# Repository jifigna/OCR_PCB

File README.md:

En la carpeta OCR_AEREO_HELTEC_V1 se encuentra el proyecto KiCad con los esquemáticos y PCB del diseño de adaptación del OCR al HELTEC V4. 

El mismo se creó utilizando la versión KiCad 10.0

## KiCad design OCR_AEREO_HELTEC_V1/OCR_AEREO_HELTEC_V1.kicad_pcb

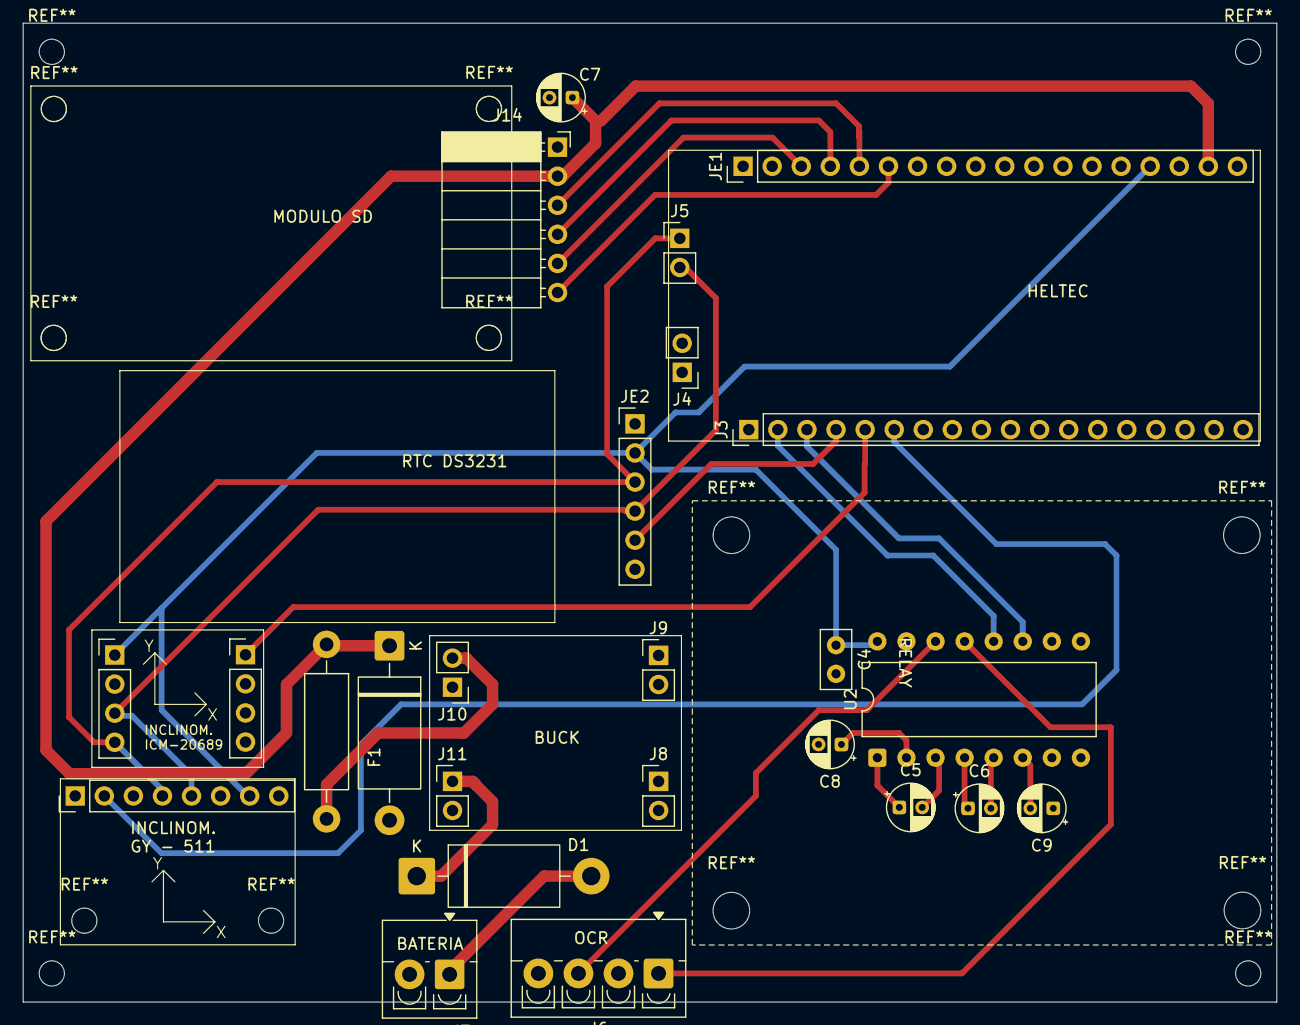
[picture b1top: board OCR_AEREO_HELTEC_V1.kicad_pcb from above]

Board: 2 copper layers, 109.5 x 85.5 mm, 25 parts (0 on the bottom side), 25 nets.

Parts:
C4: 0.1 uF; C_Disc_D5.0mm_W2.5mm_P2.50mm
C5, C6, C8, C9: 0.1uF; CP_Radial_D4.0mm_P2.00mm
C7: 470uF; CP_Radial_D4.0mm_P2.00mm
D1: 1N5402; D_DO-201AD_P15.24mm_Horizontal
D2: 1N53xxB; D_DO-201_P15.24mm_Horizontal
F1: Fuse; R_Axial_DIN0411_L9.9mm_D3.6mm_P15.24mm_Horizontal
J1, J2: Conn_01x04_Socket; PinHeader_1x04_P2.54mm_Vertical
J3: Conn_01x18_Pin; PinHeader_1x18_P2.54mm_Vertical
J4, J5, J8, J9, J10, J11: Conn_01x02_Pin; PinHeader_1x02_P2.54mm_Vertical
J6: OCR; TerminalBlock_4Ucon_1x04_P3.50mm_Vertical
J7: BATERÍA; TerminalBlock_4Ucon_1x02_P3.50mm_Vertical
J12: Conn_01x08_Socket; PinHeader_1x08_P2.54mm_Vertical
J14: MODULO SD; PinSocket_1x06_P2.54mm_Horizontal
JE1: Conn_01x18_Pin; PinHeader_1x18_P2.54mm_Vertical
JE2: RTC_DS3231; PinHeader_1x06_P2.54mm_Vertical
U2: MAX3232; DIP-16_W10.16mm

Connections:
5V: C7.1, D2.1 (K), F1.1, J14.2, JE1.17
BATERIA: D1.2 (A), J7.1
CLK_SPI: J14.5, JE1.3
CS_SD: J14.6, JE1.6
GND: C4.2, C7.2, C8.2, C9.1, D2.2 (A), J1.2, J2.4, J3.18, J6.2, J7.2, J8.1 (Pin_1_1), J9.2 (Pin_2_2), J12.6, J14.1, JE2.1, U2.15 (GND)
HELTEC_TO_OCR: J3.3, U2.11 (T1IN)
INT_INCL_1: J2.1, J3.5
INT_INCL_2: J3.6, J12.2
IN_BUCK: D1.1 (K), J11.1 (Pin_1_1)
MISO: J14.3, JE1.5
MOSI: J14.4, JE1.4
unnamed: C5.1, U2.1 (C1+)
unnamed: C5.2, U2.3 (C1-)
unnamed: C6.1, U2.4 (C2+)
unnamed: C6.2, U2.5 (C2-)
unnamed: C8.1, U2.2 (VS+)
unnamed: C9.2, U2.6 (VS-)
OCR_TO_HELTEC: J3.2, U2.12 (R1OUT)
OUT_BUCK: F1.2, J10.2 (Pin_2_2)
RX_OCR: J6.3, U2.14 (T1OUT)
SCL: J1.3, J5.2, J12.5, JE2.4
SDA: J1.4, J5.1, J12.4, JE2.3
SQW: J3.4, JE2.5
TX_OCR: J6.1, U2.13 (R1IN)
Vext: C4.1, J1.1, J12.7, JE1.15, JE2.2, U2.16 (VCC)

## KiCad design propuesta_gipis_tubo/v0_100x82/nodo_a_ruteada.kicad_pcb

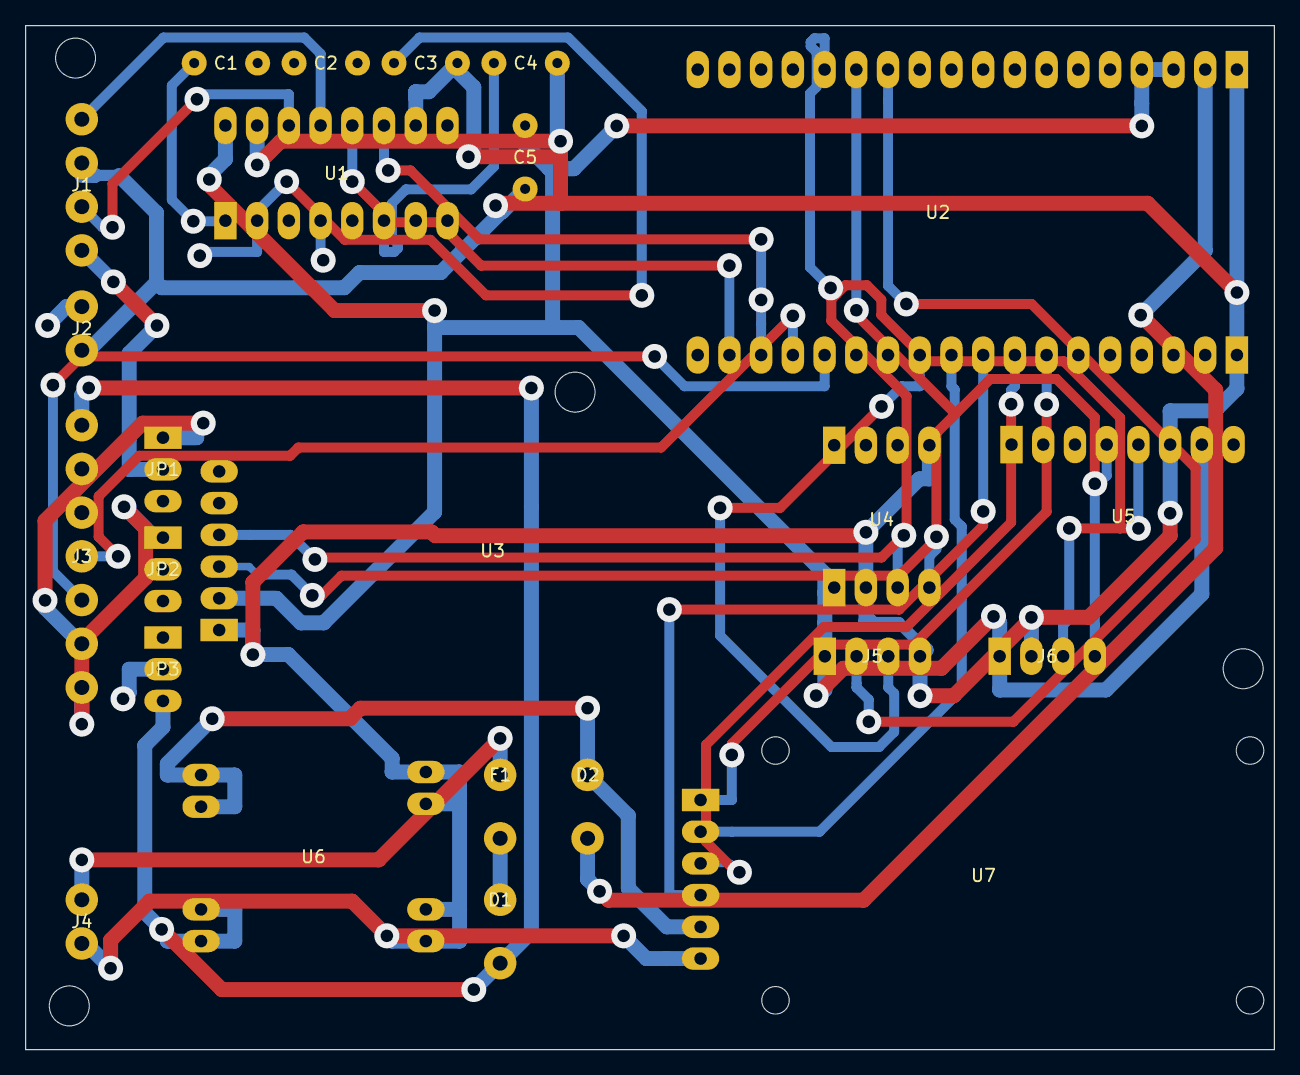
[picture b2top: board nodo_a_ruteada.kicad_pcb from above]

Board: 2 copper layers, 100.0 x 82.0 mm, 24 parts (0 on the bottom side), 32 nets.

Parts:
C1, C2, C3, C4, C5: 100n
D1, D2: 1N5819
F1: FUSE_1A
J1: OCR
J2: BIOSHUTTER
J3: RELE_EXT
J4: BAT_12V
J5: GPS
J6: I2C_AUX
JP1: OCR_PWR
JP2: SHUT_PWR
JP3: RELE_VCC
U1: MAX3232
U2: HELTEC_V4
U3: RTC_DS3231
U4: ICM-20689
U5: GY-511
U6: BUCK_5V
U7: MICROSD

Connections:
12V: D1.2, J3.1, JP1.3, JP2.3, JP3.3, U6.5, U6.6
12V_IN: F1.1, J4.1
+5V: D2.1, JP3.1, U6.1, U6.2, U7.5
+5V_H: D2.2, U2.A2
C1+: C1.1, U1.1
C1-: C1.2, U1.3
C2+: C2.1, U1.4
C2-: C2.2, U1.5
F_OUT: D1.1, F1.2
GND: C3.2, C4.2, C5.2, J1.2, J2.2, J3.3, J4.2, J5.4, J6.2, U1.10, U1.15, U2.A1, U2.B1, U3.1, U4.4, U4.6, U5.6, U6.3, U6.4, U6.7, U6.8, U7.6
GPS_RX: J5.2, U2.A12
GPS_TX: J5.3, U2.B11
NO1: J3.6, JP1.1
NO2: J3.7, JP2.1
OCR_RXD: U1.12, U2.B17
OCR_TXD: U1.11, U2.B16
RELE1: J3.4, U2.B15
RELE2: J3.5, U2.B14
RX_OCR: J1.3, U1.14
SCL: J6.3, U2.A14, U3.4, U4.7, U5.5
SDA: J6.4, U2.A13, U3.3, U4.8, U5.4
SD_CS: U2.B7, U7.1
SD_MISO: U2.B9, U7.4
SD_MOSI: U2.B8, U7.3
SD_SCK: U2.B10, U7.2
TX_OCR: J1.1, U1.13
V+: C3.1, U1.2
V+_OCR: J1.4, JP1.2
V+_SHUT: J2.1, JP2.2
V-: C4.1, U1.6
VCC_RELE: J3.2, JP3.2
VE: C5.1, J5.1, J6.1, U1.16, U2.A3, U2.A4, U3.2, U4.5, U5.7
